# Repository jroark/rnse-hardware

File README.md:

# Hardware for the RNS-E

KiCad designs of boards that go with the software for the Audi RNS-E
(the rnse emulator and the kit and programs built on it). Each board is
a directory of its own, with its README:

| Board | What it is | State |
|---|---|---|
| [`nes-can`](nes-can/README.md) | two original NES controllers on the infotainment CAN bus, for the NES port; ATtiny1616 firmware in `nes-can/firmware` | revision A, not built |
| [`ps2-can`](ps2-can/README.md) | a PS/2 keyboard and mouse on the CAN bus | revision A, not fabricated or electrically tested; no firmware yet |
| [`sdbridge-card`](sdbridge-card/README.md) | the SD bridge (an RP2040 that answers as an SD card) on a board the outline of a full-size SD card, powered by the slot | PCB rev B; CAD and electrical checks done, not yet qualified in a unit |

Paths in this directory's files are written from its own root
(`hardware/` in the rnse repository).

## Fabrication files

Gerbers, drill files, BOMs and placement files are committed as
generated by each board's scripts. The ZIP archives a fabricator wants
are not: each board's script makes them (`sh sdbridge-card/fab.sh`,
`python3 nes-can/package.py`).

## Using them

These are prototypes. ERC and DRC results describe checks of the CAD
data, not a built board, and none of them is qualified for a vehicle.
Wiring anything into a car's electrical system or a unit's CAN bus is at
your own risk, as are your unit, your discs and your data. Software run
on a unit with one of these boards has to keep the display's fold-down
and the disc's eject working at all times (see `CLAUDE.md` in the
repository that builds it).

## Licence

CERN-OHL-P-2.0 ([LICENSE](LICENSE)).

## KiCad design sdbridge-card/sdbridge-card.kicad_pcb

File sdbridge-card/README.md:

# RNS-E 192 SD bridge card · PCB Rev B

This is the slot-powered version of the Pico SD bridge. The assembled carrier has the outline of a full-size SD card. A bare RP2040 and 2 MiB Winbond flash sit inside it. The phone plugs into a USB-A receptacle wired behind the modified cage. All wiring stays behind the cage and clear of the screen opening.

Open **sdbridge-card.kicad_pro** in KiCad 10 with its standard libraries installed. The project includes local symbols and a card-side contact footprint. The CAD and electrical checks below are complete. The new assembly still needs qualification in an actual 192.

- **PCB order** — Gerbers, drill, layer job and [fabrication notes](manufacturing/fabrication.txt), packed into `manufacturing/sdbridge-card-revB.zip` by `sh fab.sh` (KiCad 10's `kicad-cli`; the ZIP is generated, not committed). Quote the **two-layer, 0.40 mm** finished stack and selective hard gold explicitly.
- **PCB assembly** — [BOM with manufacturer part numbers](manufacturing/bom.csv) and [top-side placement](manufacturing/placement.csv). J1 is the nine-finger pattern. TP1–7 are bare probe pads.
- **Carrier** — [dimensioned assembly](mechanical/assembly.svg), [carrier STEP](mechanical/carrier.step), [tray STL](mechanical/tray.stl), [lid STL](mechanical/lid.stl) and [solid fit gauge](mechanical/fit-gauge.stl). STL dimensions are millimetres. The KiCad board outline is the insert. Both insulating shell halves are required for the finished profile.
- **Installation** — [rear cage wiring drawing](mechanical/cage-wiring.svg). It identifies tails by electrical continuity, since the board-side tail order depends on the socket.

## Cage wiring

Use the second slot for the bridge if the first slot holds the viewer software. Disconnect power and remove all cards before altering the cage. Identify each spring and its solder tail with a continuity meter. On the contact face, the finger beside the diagonal corner is pin **9**. The narrow finger at the far end of the row is pin **8**.

| Card finger | Card circuit | Back of the modified cage |
|---|---|---|
| 1 · DAT3 | Isolated gold land | Original connection |
| 2 · CMD | R2, 100 Ω to GP3 | Original connection |
| 3, 6 · VSS | Ground | Common return for card, VBUS source and USB-A pin 4 |
| 4 · VDD | Slot 3.3 V to RP2040 and flash | Original 3.3 V connection |
| 5 · CLK | R1, 100 Ω to GP2 | Original connection |
| 7 · DAT0 | R3, 100 Ω to GP4 | Original connection |
| **8 · DAT1** | **R4, 27 Ω to USB_DP** | **Isolated tail to USB-A pin 3, D+** |
| **9 · DAT2** | **R5, 27 Ω to USB_DM** | **Isolated tail to USB-A pin 2, D−** |

Lift or otherwise isolate just tails 8 and 9 from their original RNS-E data traces. Leave both springs able to move. Verify an open circuit from each lifted tail to its former board pad and between the two lifted tails, with the card and harness disconnected. Attach the two data wires as a short USB pair, with strain relief on the stationary housing. Check continuity end to end to the **numbered pins of the actual receptacle**.

Supply USB-A pin 1 from a separate switched, regulated, current-limited **5 V** source behind the cage, sized for the phone and cable. Join its return to card ground. Sequence phone VBUS with the powered bridge, including shutdown. The card uses only slot 3.3 V. Verify isolation between USB 5 V and SD pin 4 before applying power. Mark the modified socket for this bridge because the original four-bit SD data path has been repurposed.

## Mechanical assembly

The latch, fixed write-enable profile, card-detect edge, recessed contact channels and 22 mm lower shoulder are in the carrier. The electronic insert measures **21.50 × 30.60 mm**. The assembled outline measures **24.00 × 32.00 × 2.10 mm**. The geometry follows the card views and contact numbering in figures 2-1 and 2-2 of the SanDisk manual. [SanDisk SD Card Product Manual, revision 2.2](https://www.openimpulse.com/blog/wp-content/uploads/wpsc/downloadables/SD-Card-Simplified-Specification.pdf)

1. Make the solid gauge at 1:1. For the installed parts, use dimensionally stable insulating material suitable for the cabin temperature, such as precision-machined polycarbonate. The lid has a **0.10 mm roof** over U1 and Y1. Confirm the manufacturing process can hold it. Remove sharp edges, support marks and flash, especially at the nose and latch.
2. Check the unpowered gauge in the actual cage against a known-good card. Match insertion force, latched depth, card-detect switch operation and push-to-release. With the gauge fully latched, check screen closing and reopening and inspect for rub marks. Stop if it binds. A successful gauge test qualifies the outline only.
3. Program and bench-test the PCB before closing the lid. Seat it gold face down on the hard lands. Use small amounts of nonconductive adhesive in the two underside reservoirs and hold the board flat against the lands while curing. Keep adhesive out of the spring channels. Verify that all nine fingers are exposed.
4. Fit the lid with its pockets toward the components. Use **0.025 mm** bond film on the mating perimeter. Keep the seam flush. Check that the lid stays flat over U1 under light pressure and that the carrier cannot separate during removal.
5. Inspect the finished card. Target 24.00 and 32.00 mm within ±0.05 mm, and 2.10 mm within ±0.04 mm. From the gold datum the tray floor reaches −0.55 mm, lid exterior +1.55 mm and U1 pocket roof +1.45 mm. Hold the assembled roof within ±0.02 mm and measure the populated height before bonding. With a 0.44 mm finished PCB, 0.90 mm IC, 0.06 mm solder stand-off and 0.01 mm seating allowance, the limiting roof clearance is **0.02 mm**. Reject interference, warping, contamination or any protruding adhesive. Repeat the gauge checks with the actual bonded assembly.

PCB Rev B uses the Rev A tray and lid. The parametric carrier source reads the KiCad placement CSV. Run `python mechanical/carrier.py` with CadQuery 2.8 to regenerate the mechanical solids after placement changes. Use KiCad's STEP export with user origin **100 × 100 mm** to place the populated PCB into the shell's coordinate system. Align the lowest gold surface to Z = 0.

## Programming and checkout

Use the **Pico** firmware target. GP25 drives the active-high green LED. GP0 carries the 115200 baud UART log. The existing design uses GP2–4 for the one-bit SD interface. [Prototype and firmware](https://github.com/jroark/rnse-sdbridge/blob/main/docs/sdbridge.md) · [Raspberry Pi RP2040 hardware design guide](https://datasheets.raspberrypi.com/rp2040/hardware_design_with_rp2040.pdf)

| Pad | TP1 | TP2 | TP3 | TP4 | TP5 | TP6 | TP7 |
|---|---|---|---|---|---|---|---|
| Signal | GND | 3.3 V | SWDIO | SWCLK | RUN | BOOTSEL | GP0 TX |

1. On the bench, outside the cage, power TP2 from a regulated current-limited 3.3 V supply with return at TP1. Verify the core regulator comes up and confirm SWD identification. BOOTSEL connects to flash CS through R8. For USB boot, ground TP6, pulse TP5 low and release reset, then release TP6. A bench USB fixture connects PC D+, D− and GND to fingers 8, 9 and 3/6. Keep PC VBUS isolated from the card. Copy `sdbridge/out/pico/SDLINK.UF2` to the boot volume. Building SDLINK requires the existing build's `AA_CERT` and `AA_KEY` inputs.
2. Disconnect the bench supply before seating the card in the powered installation. On the unit, test cold power-up with the card latched and insertion after startup. Measure slot 3.3 V and card current during flash boot, enumeration and sustained transfer. Capture the GP0 log on the bench or an instrumented open fixture. Confirm the first SD negotiation completes from slot power.
3. Verify a complete read and content check of `LINKTEST.BIN`. Connect the phone, confirm USB full-speed enumeration and the Android Auto handshake, and exercise simultaneous USB video reception and SD reads. Repeat after a phone disconnect and a head-unit power cycle.
4. This delivery contains card hardware only. For a head-unit hardware run, use a verified image with responsive physical display and disc-eject handling during reads and error screens. In the SDK, `panel_service()` polls the faceplate. `KEY_DISPLAY` calls `display_toggle()`. The separate `KEY_CD_EJECT` calls `cd_eject()`, which issues ATAPI ALLOW MEDIUM REMOVAL then START STOP UNIT with LoEj set. Verify screen opening and actual disc expulsion with the bridge installed. Keep stock updater handoffs out of the test. [Faceplate and ATAPI path](https://github.com/jroark/rnse-sdk/blob/main/src/cd.c) · [Display motor control](https://github.com/jroark/rnse-sdk/blob/main/src/display.c)

## Verification record

KiCad 10.0.8 ERC and DRC passed with zero warnings or errors, zero unconnected pads and zero schematic parity issues. The exported B.Mask contains nine finger openings. All 42 finished drill holes clear the nine gold wipe surfaces. The placement file and BOM cover the same 29 populated designators. The existing Pico SDLINK UF2 targets RP2040 flash and fits within the 2 MiB device. The nominal populated STEP model measured 1.33 mm above its lowest gold surface. A solid intersection check found zero overlap with either shell half. The straight coupled USB section has ground underneath on B.Cu. A nominal cross-section estimate gives approximately 90 Ω differential for 0.32 mm traces at 0.14 mm spacing. The split to the SD fingers and the rear wiring need bench verification. Physical cage fit, screen travel, contact reliability, slot supply margin, USB signal quality and operation of this board revision remain bench and hardware tests.

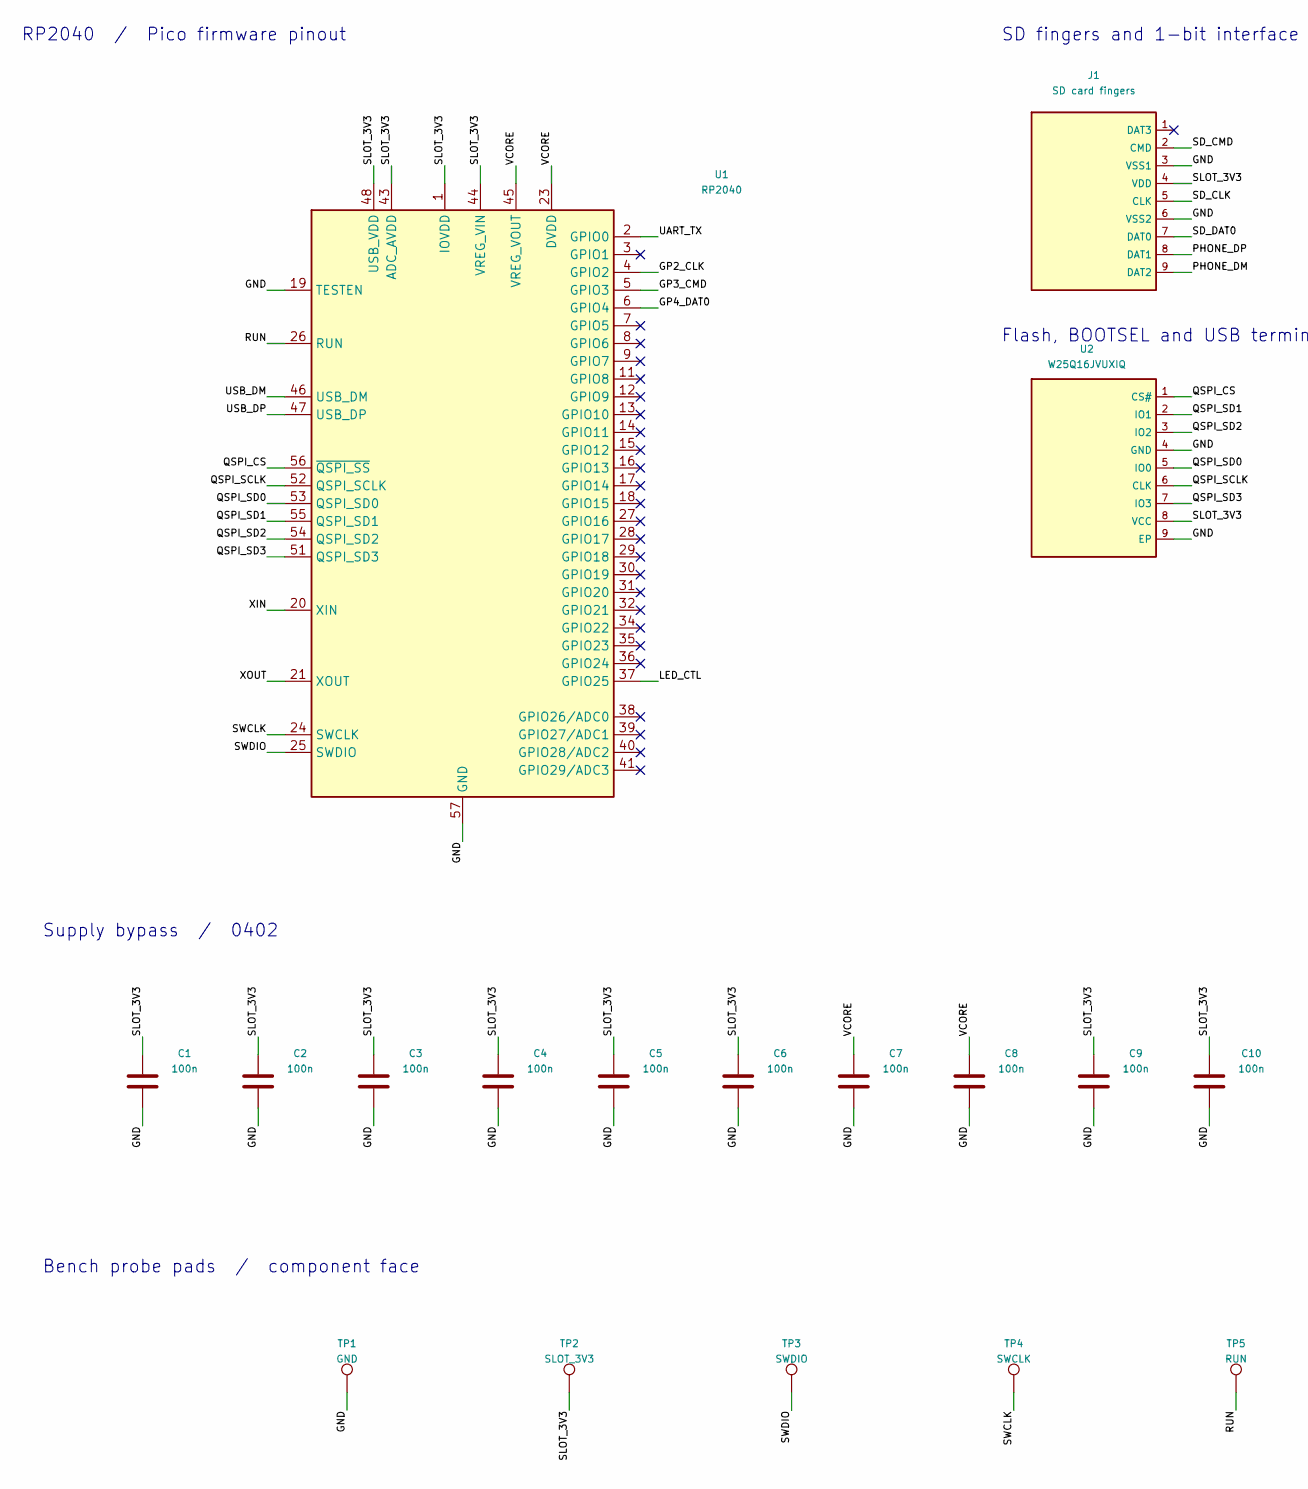
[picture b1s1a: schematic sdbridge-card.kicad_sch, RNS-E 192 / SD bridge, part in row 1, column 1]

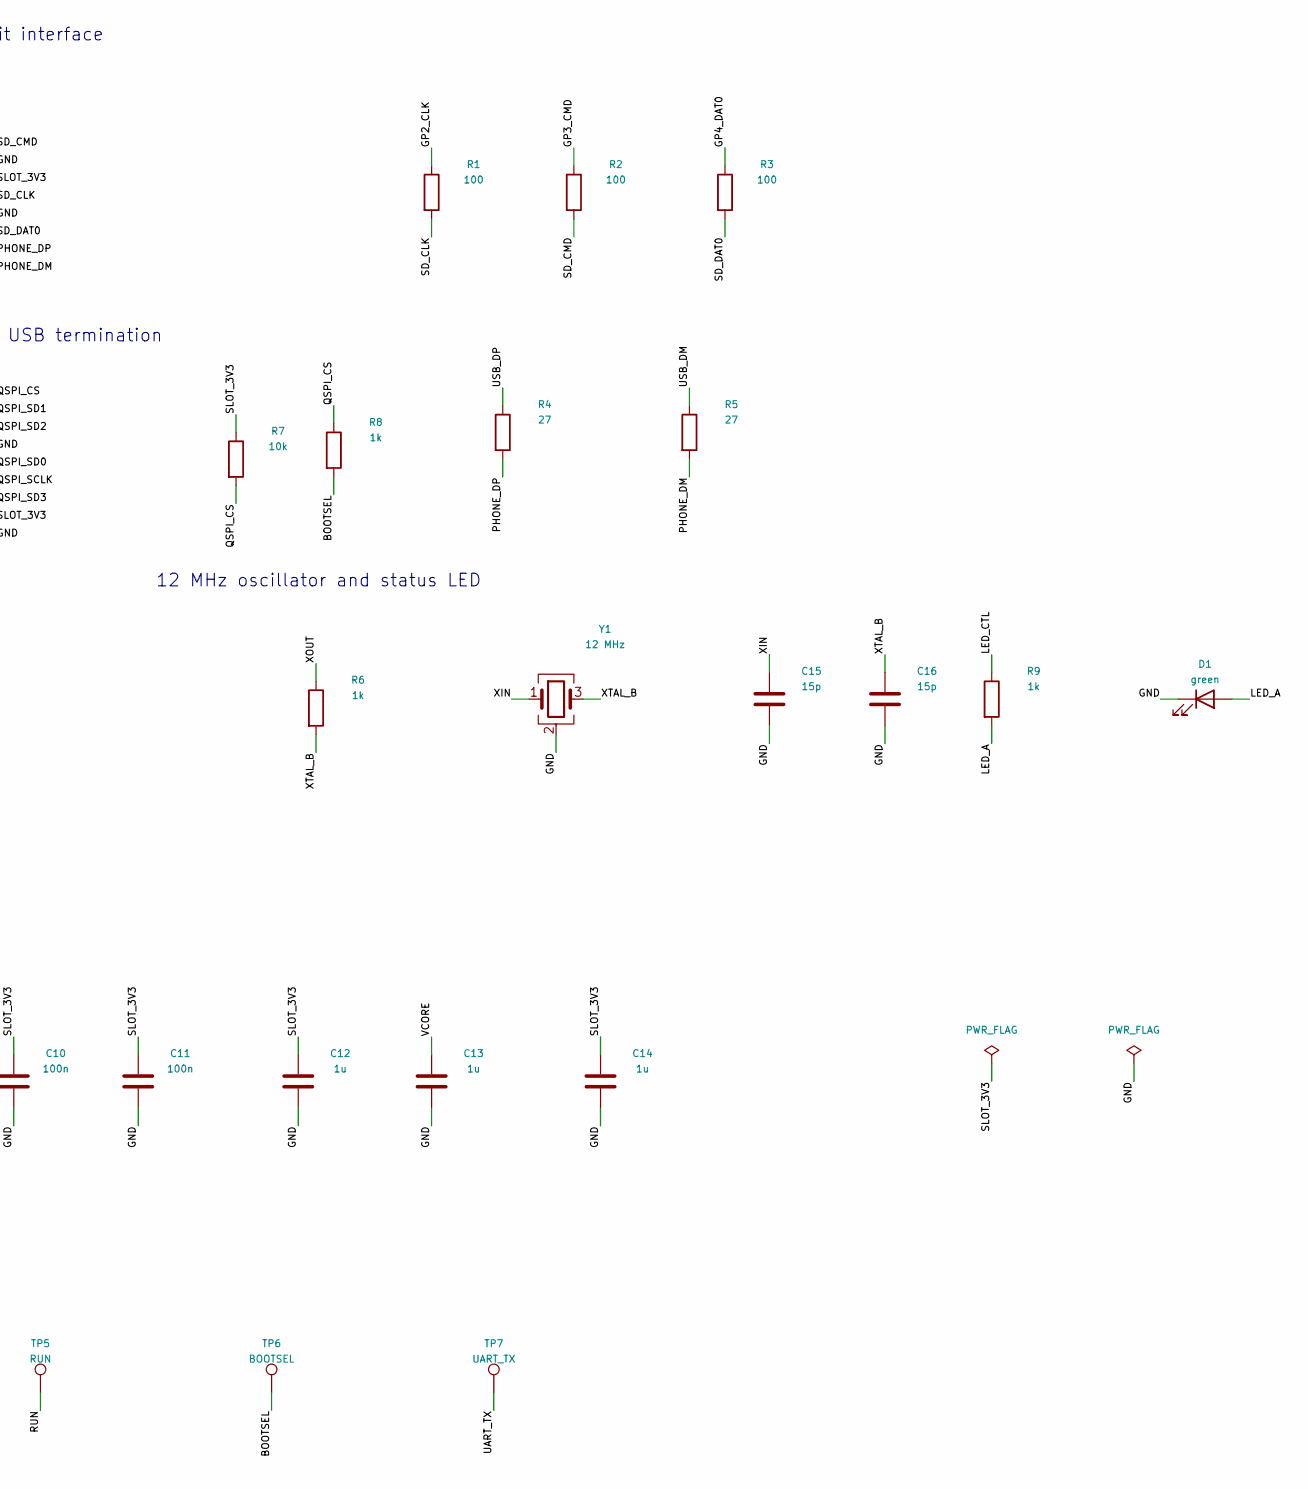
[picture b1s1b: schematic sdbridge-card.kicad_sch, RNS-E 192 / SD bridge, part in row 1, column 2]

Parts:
C1, C2, C3, C4, C5, C6, C7, C8, C9, C10, C11: 100n; C_0402_1005Metric
C12, C13, C14: 1u; C_0402_1005Metric
C15, C16: 15p; C_0402_1005Metric
D1: green; LED_0402_1005Metric
J1: SD card fingers; Card_Fingers
R1, R2, R3: 100; R_0402_1005Metric
R4, R5: 27; R_0402_1005Metric
R6, R8, R9: 1k; R_0402_1005Metric
R7: 10k; R_0402_1005Metric
TP1: GND; TestPoint_Pad_D1.0mm
TP2: SLOT_3V3; TestPoint_Pad_D1.0mm
TP3: SWDIO; TestPoint_Pad_D1.0mm
TP4: SWCLK; TestPoint_Pad_D1.0mm
TP5: RUN; TestPoint_Pad_D1.0mm
TP6: BOOTSEL; TestPoint_Pad_D1.0mm
TP7: UART_TX; TestPoint_Pad_D1.0mm
U1: RP2040; QFN-56-1EP_7x7mm_P0.4mm_EP3.2x3.2mm
U2: W25Q16JVUXIQ; Winbond_USON-8-1EP_3x2mm_P0.5mm_EP0.2x1.6mm
Y1: 12 MHz; Crystal_SMD_3225-4Pin_3.2x2.5mm

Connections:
/BOOTSEL: R8.2, TP6.1
/GND: C1.2, C2.2, C3.2, C4.2, C5.2, C6.2, C7.2, C8.2, C9.2, C10.2, C11.2, C12.2, C13.2, C14.2, C15.2, C16.2, D1.1 (K), J1.3 (VSS1), J1.6 (VSS2), TP1.1, U1.19 (TESTEN), U1.57 (GND), U2.4 (GND), U2.9 (EP), Y1.2 (G), Y1.4 (G)
/GP2_CLK: R1.1, U1.4 (GPIO2)
/GP3_CMD: R2.1, U1.5 (GPIO3)
/GP4_DAT0: R3.1, U1.6 (GPIO4)
/LED_A: D1.2 (A), R9.2
/LED_CTL: R9.1, U1.37 (GPIO25)
/PHONE_DM: J1.9 (DAT2), R5.2
/PHONE_DP: J1.8 (DAT1), R4.2
/QSPI_CS: R7.2, R8.1, U1.56 (~QSPI_SS), U2.1 (CS#)
/QSPI_SCLK: U1.52 (QSPI_SCLK), U2.6 (CLK)
/QSPI_SD0: U1.53 (QSPI_SD0), U2.5 (IO0)
/QSPI_SD1: U1.55 (QSPI_SD1), U2.2 (IO1)
/QSPI_SD2: U1.54 (QSPI_SD2), U2.3 (IO2)
/QSPI_SD3: U1.51 (QSPI_SD3), U2.7 (IO3)
/RUN: TP5.1, U1.26 (RUN)
/SD_CLK: J1.5 (CLK), R1.2
/SD_CMD: J1.2 (CMD), R2.2
/SD_DAT0: J1.7 (DAT0), R3.2
/SLOT_3V3: C1.1, C2.1, C3.1, C4.1, C5.1, C6.1, C9.1, C10.1, C11.1, C12.1, C14.1, J1.4 (VDD), R7.1, TP2.1, U1.1 (IOVDD), U1.10 (IOVDD), U1.22 (IOVDD), U1.33 (IOVDD), U1.42 (IOVDD), U1.43 (ADC_AVDD), U1.44 (VREG_VIN), U1.48 (USB_VDD), U1.49 (IOVDD), U2.8 (VCC)
/SWCLK: TP4.1, U1.24 (SWCLK)
/SWDIO: TP3.1, U1.25 (SWDIO)
/UART_TX: TP7.1, U1.2 (GPIO0)
/USB_DM: R5.1, U1.46 (USB_DM)
/USB_DP: R4.1, U1.47 (USB_DP)
/VCORE: C7.1, C8.1, C13.1, U1.23 (DVDD), U1.45 (VREG_VOUT), U1.50 (DVDD)
/XIN: C15.1, U1.20 (XIN), Y1.1
/XOUT: R6.1, U1.21 (XOUT)
/XTAL_B: C16.1, R6.2, Y1.3

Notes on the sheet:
Bench probe pads / component face
Supply bypass / 0402
RP2040 / Pico firmware pinout
12 MHz oscillator and status LED
SD fingers and 1-bit interface
Flash, BOOTSEL and USB termination

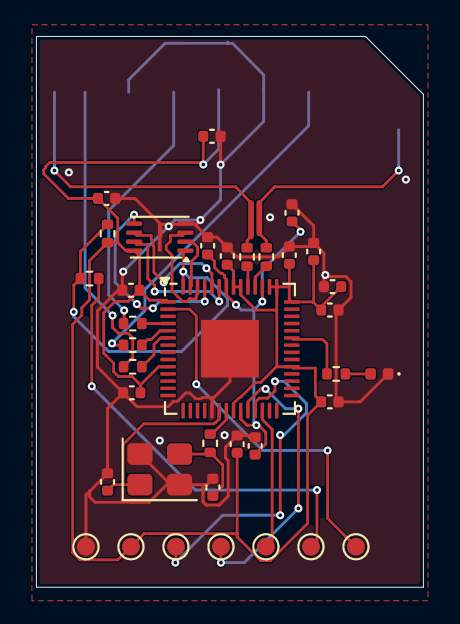
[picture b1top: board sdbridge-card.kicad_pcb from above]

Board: 2 copper layers, 21.5 x 30.6 mm, 37 parts (0 on the bottom side), 29 nets.

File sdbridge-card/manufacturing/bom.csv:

Designators,Quantity,Value,Manufacturer part number,Footprint
U1,1,RP2040,SC0914,Package_DFN_QFN:QFN-56-1EP_7x7mm_P0.4mm_EP3.2x3.2mm
U2,1,W25Q16JVUXIQ,W25Q16JVUXIQ,Package_SON:Winbond_USON-8-1EP_3x2mm_P0.5mm_EP0.2x1.6mm
"R1, R2, R3",3,100,RC0402FR-07100RL,Resistor_SMD:R_0402_1005Metric
"R4, R5",2,27,RC0402FR-0727RL,Resistor_SMD:R_0402_1005Metric
"R6, R8, R9",3,1k,RC0402FR-071KL,Resistor_SMD:R_0402_1005Metric
R7,1,10k,RC0402FR-0710KL,Resistor_SMD:R_0402_1005Metric
D1,1,green,APG1005CGCK-T,LED_SMD:LED_0402_1005Metric
Y1,1,12 MHz,ABM8-272-T3,Crystal:Crystal_SMD_3225-4Pin_3.2x2.5mm
"C1, C2, C3, C4, C5, C6, C7, C8, C9, C10, C11",11,100n,GRM155R71C104KA88D,Capacitor_SMD:C_0402_1005Metric
"C12, C13, C14",3,1u,GRM155R60J105KE19D,Capacitor_SMD:C_0402_1005Metric
"C15, C16",2,15p,GRM1555C1H150JA01D,Capacitor_SMD:C_0402_1005Metric
